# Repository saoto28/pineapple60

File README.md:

# pineapple60
ergonomic keyboard with Trackpoint

The purposes of this project.
- Install it in ThinkPad

## pineapple-F
Pinapple-Fold, Foldable ergonomic keyboard  
[mockup video on twitter](https://x.com/saoto28/status/2055436990498451473)

## pineapple-D
Pineapple-Deep, under consideration

## p60P
Pineapple60-Popup, installing a Pop-up keyboard on a ThinkPad.  

[Mockup video](https://youtu.be/z3uHgcyWICA)

## p60C
2026, Pineapple60-Convertible, Three-dimensional ergonomic arrangement and a flat, compact convertible. A patent allowed in Japan.

1st prototype 

[Video](https://x.com/saoto28/status/2051869687362077159)

Project repository: 
https://github.com/saoto28/pineapple60c.git

## p60S
2025, pineapple60s

Row-Staggered Ergonomic (Alice) keyboard with Kailh PG1316 for installing ThinkPad X13 Gen2

I forgot why it was named "S".

For this modification, I chose the target PC for the following reasons:
- It has a Trackpoint
- The keyboard can be easily replaced (the latest ThinkPads are getting difficult)
- The Trackpoint buttons should be on the case, not on the keyboard unit. Otherwise, I would need to attach the buttons to the keyboard I was making.

The following ThinkPads meet the above requirements:
- T440 to T460, and so on
- T460s and T470s
- X13 Gen2 and Gen3

X240 to X270 are also close, but we need to remove the motherboard to remove the keyboard.

Project repository: 
https://github.com/saoto28/pineapple60s.git

How to make (in Japanese): https://note.com/saoto28/n/n716b7ca2e1f9

## p0

Extra edition. Trackpoint module installation.

2021-10 Add the Trackpoint module of ThinkPad X100 on the Microsoft Ergonomic Keyboard.

[How to install the Trackpoint module in the MS ergonomic keyboard](p0/How_to_modify_MS_ergonomic_keyboard.pdf)

~~## p60X~~

~~Variable key layout board for researching ergonomic keyboard layouts~~

~~< 2021-09 coming soon >~~

## p50V

V-style key layout [board](p50V/README.md)

2021-08 installed on my T470s

## p60-03

third prototype [pcb](p60-03/README.md)

2021-05 p60-03b 

[how to make the ergonomic Trackpoint keyboard](how_to_make_ergonomic_trackpoint_keyboard.md)

## p4

2021-03 key layout testing [module](p4/README.md)

## p60-02

2020-12 second prototype [pcb](p60-02/README.md)

## p60-01

2020-10 first prototype [pcb](p60-01/README.md)

## pre-pineapple

2020-08 I tried to make an ergonomic keyboard for my ThinkPad T470s, by disassembling and modifying the spare keyboard. But, gave up.

## SNS

https://twitter.com/saoto28

https://www.reddit.com/user/saoto28/posts/

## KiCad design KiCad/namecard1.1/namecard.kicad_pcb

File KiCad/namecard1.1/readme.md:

# KiCAD format for the Arduino shield  namecard ver.1.1

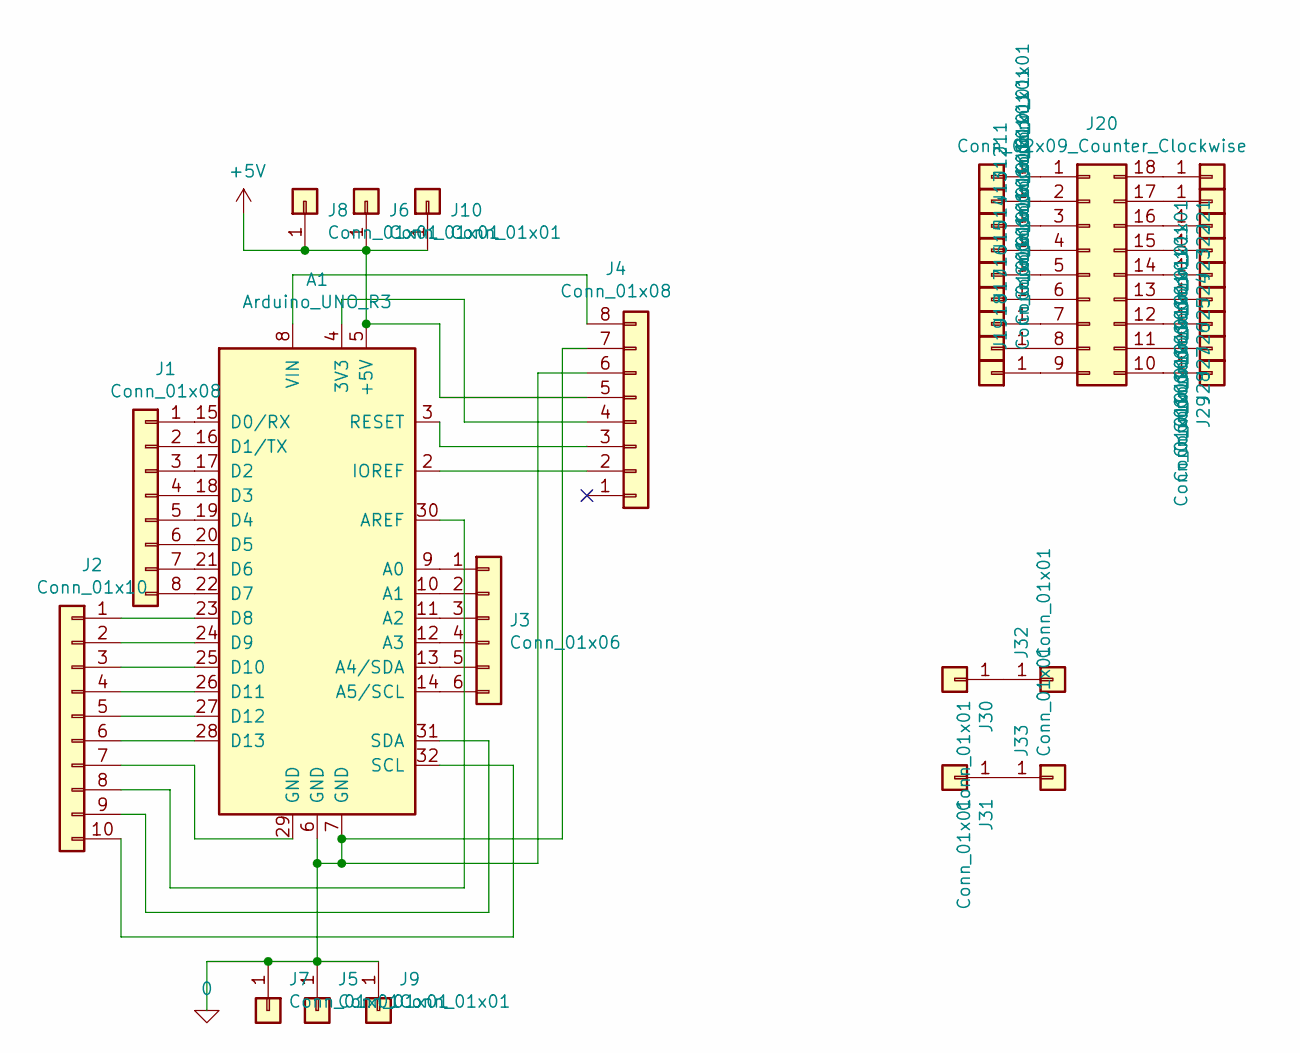
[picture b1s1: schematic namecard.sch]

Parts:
A1: Arduino_UNO_R3
J1, J4: Conn_01x08; PinHeader_1x08_P2.54mm_Vertical
J2: Conn_01x10; PinHeader_1x10_P2.54mm_Vertical
J3: Conn_01x06; PinHeader_1x06_P2.54mm_Vertical
J5, J6, J7, J8, J9, J10, J30, J31, J32, J33: Conn_01x01; SolderWirePad_1x01_Drill1.0mm_1.7
J11, J12, J13, J14, J15, J16, J17, J18, J19, J21, J22, J23, J24, J25, J26, J27, J28, J29: Conn_01x01; SolderWirePad_1x01_Drill1.0mm_1.7_no-mark
J20: Conn_02x09_Counter_Clockwise; SOP-18_7x12.5mm_P1.27mm_mod

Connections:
unnamed: A1.1 (NC), A1.29 (GND), J2.7
unnamed: A1.2 (IOREF), J4.2
unnamed: A1.3 (RESET), J4.3
unnamed: A1.4 (3V3), J4.4
unnamed: A1.8 (VIN), J4.8
unnamed: A1.9 (A0), J3.1
unnamed: A1.10 (A1), J3.2
unnamed: A1.11 (A2), J3.3
unnamed: A1.12 (A3), J3.4
unnamed: A1.13 (A4/SDA), J3.5
unnamed: A1.14 (A5/SCL), J3.6
unnamed: A1.15 (D0/RX), J1.1
unnamed: A1.16 (D1/TX), J1.2
unnamed: A1.17 (D2), J1.3
unnamed: A1.18 (D3), J1.4
unnamed: A1.19 (D4), J1.5
unnamed: A1.20 (D5), J1.6
unnamed: A1.21 (D6), J1.7
unnamed: A1.22 (D7), J1.8
unnamed: A1.23 (D8), J2.1
unnamed: A1.24 (D9), J2.2
unnamed: A1.25 (D10), J2.3
unnamed: A1.26 (D11), J2.4
unnamed: A1.27 (D12), J2.5
unnamed: A1.28 (D13), J2.6
unnamed: A1.30 (AREF), J2.8
unnamed: A1.31 (SDA), J2.9
unnamed: A1.32 (SCL), J2.10
unnamed: J11.1, J20.1
unnamed: J12.1, J20.2
unnamed: J13.1, J20.3
unnamed: J14.1, J20.4
unnamed: J15.1, J20.5
unnamed: J16.1, J20.6
unnamed: J17.1, J20.7
unnamed: J18.1, J20.8
unnamed: J19.1, J20.9
unnamed: J20.10, J29.1
unnamed: J20.11, J28.1
unnamed: J20.12, J27.1
unnamed: J20.13, J26.1
unnamed: J20.14, J25.1
unnamed: J20.15, J24.1
unnamed: J20.16, J23.1
unnamed: J20.17, J22.1
unnamed: J20.18, J21.1
unnamed: J30.1, J32.1
unnamed: J31.1, J33.1

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
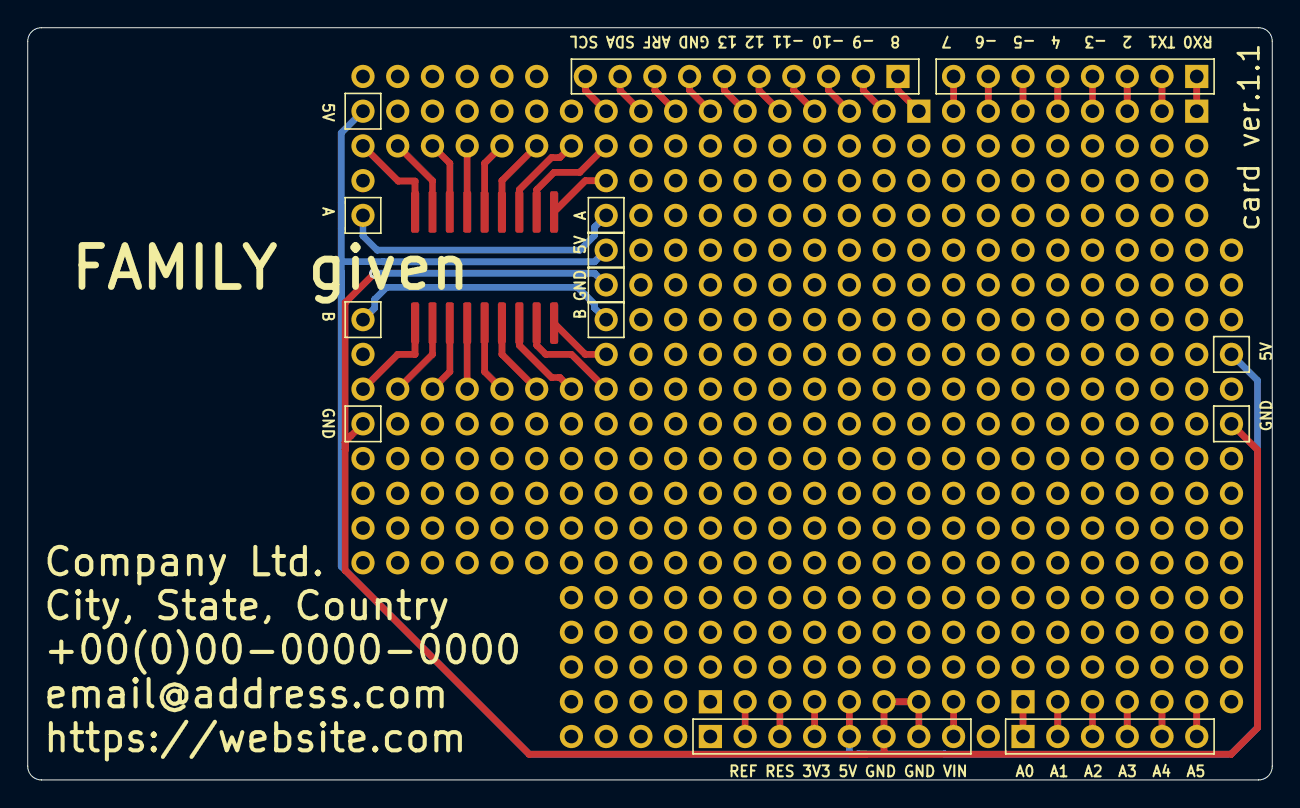
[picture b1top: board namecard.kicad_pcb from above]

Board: 2 copper layers, 91.0 x 55.0 mm, 34 parts (1 on the bottom side), 50 nets.

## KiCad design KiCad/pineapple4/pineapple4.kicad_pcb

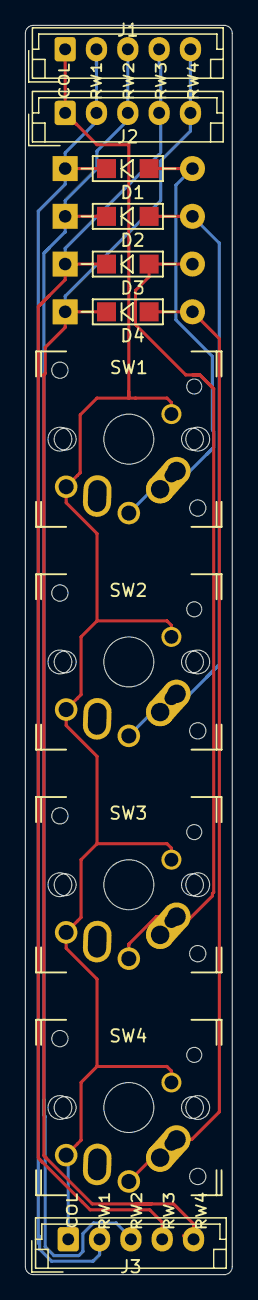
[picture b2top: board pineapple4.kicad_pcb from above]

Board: 2 copper layers, 16.5 x 99.7 mm, 11 parts (0 on the bottom side), 9 nets.

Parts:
D1, D2, D3, D4: D; Diode_TH_SOD123
J1, J2, J3: Conn_01x05; JST_EH_B5B-EH-A_1x05_P2.50mm_Vertical
SW1, SW2, SW3, SW4: SW_Push; MX-ALPS-Choc-X-straight-oneside

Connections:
unnamed: D1.1, J1.2, J2.2, J3.2
unnamed: D1.2, SW1.2
unnamed: D2.1, J1.3, J2.3, J3.3
unnamed: D2.2, SW2.2
unnamed: D3.1, J1.4, J2.4, J3.4
unnamed: D3.2, SW3.2
unnamed: D4.1, J1.5, J2.5, J3.5
unnamed: D4.2, SW4.2
unnamed: J1.1, J2.1, J3.1, SW1.1, SW2.1, SW3.1, SW4.1

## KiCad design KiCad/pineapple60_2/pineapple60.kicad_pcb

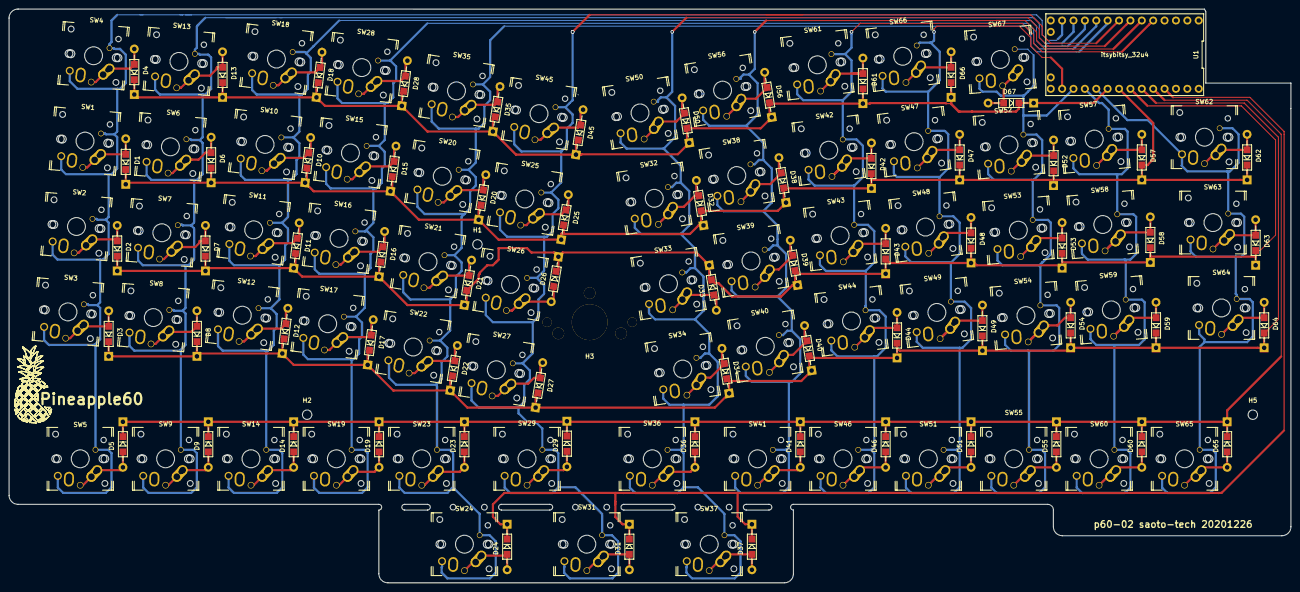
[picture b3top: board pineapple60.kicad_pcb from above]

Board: 2 copper layers, 286.0 x 128.0 mm, 137 parts (0 on the bottom side), 85 nets.

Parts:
D1, D2, D3, D4, D5, D6, D7, D8, D9, D10, D11, D12, D13, D14, D15, D16, D17, D18, D19, D20, D21, D22, D23, D24, D25, D26, D27, D28, D29, D31, D32, D33, D34, D35, D36, D37, D38, D39, D40, D41, D42, D43, D44, D45, D46, D47, D48, D49, D50, D51, D52, D53, D54, D55, D56, D57, D58, D59, D60, D61, D62, D63, D64, D65, D66, D67: D; Diode_TH_SOD123
H1, H2, H5: MountingHole; MountingHole_2.1mm
H3: MountingHole; Trackpoint_KT1255
SW1, SW2, SW3, SW4, SW5, SW6, SW7, SW8, SW9, SW10, SW11, SW12, SW13, SW14, SW15, SW16, SW17, SW18, SW19, SW20, SW21, SW22, SW23, SW25, SW26, SW27, SW28, SW31, SW32, SW33, SW34, SW35, SW38, SW39, SW40, SW41, SW42, SW43, SW44, SW45, SW46, SW47, SW48, SW49, SW50, SW51, SW52, SW53, SW54, SW55, SW56, SW57, SW58, SW59, SW60, SW61, SW65, SW66, SW67: SW_Push; MX-ALPS-Choc-X-straight-oneside
SW24, SW29, SW36, SW37, SW62, SW63, SW64: SW_Push; MX-ALPS-Choc-X-straight-1.5U
U1: itsybitsy_32u4; itsybitsy_32u4_open

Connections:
unnamed: D1.2, SW1.2
unnamed: D2.2, SW2.2
unnamed: D3.2, SW3.2
unnamed: D4.2, SW4.2
unnamed: D5.2, SW5.2
unnamed: D6.2, SW6.2
unnamed: D7.2, SW7.2
unnamed: D8.2, SW8.2
unnamed: D9.2, SW9.2
unnamed: D10.2, SW10.2
unnamed: D11.2, SW11.2
unnamed: D12.2, SW12.2
unnamed: D13.2, SW13.2
unnamed: D14.2, SW14.2
unnamed: D15.2, SW15.2
unnamed: D16.2, SW16.2
unnamed: D17.2, SW17.2
unnamed: D18.2, SW18.2
unnamed: D19.2, SW19.2
unnamed: D20.2, SW20.2
unnamed: D21.2, SW21.2
unnamed: D22.2, SW22.2
unnamed: D23.2, SW23.2
unnamed: D24.2, SW24.2
unnamed: D25.2, SW25.2
unnamed: D26.2, SW26.2
unnamed: D27.2, SW27.2
unnamed: D28.2, SW28.2
unnamed: D29.2, SW29.2
unnamed: D31.2, SW31.2
unnamed: D32.2, SW32.2
unnamed: D33.2, SW33.2
unnamed: D34.2, SW34.2
unnamed: D35.2, SW35.2
unnamed: D36.2, SW36.2
unnamed: D37.2, SW37.2
unnamed: D38.2, SW38.2
unnamed: D39.2, SW39.2
unnamed: D40.2, SW40.2
unnamed: D41.2, SW41.2
unnamed: D42.2, SW42.2
unnamed: D43.2, SW43.2
unnamed: D44.2, SW44.2
unnamed: D45.2, SW45.2
unnamed: D46.2, SW46.2
unnamed: D47.2, SW47.2
unnamed: D48.2, SW48.2
unnamed: D49.2, SW49.2
unnamed: D50.2, SW50.2
unnamed: D51.2, SW51.2
unnamed: D52.2, SW52.2
unnamed: D53.2, SW53.2
unnamed: D54.2, SW54.2
unnamed: D55.2, SW55.2
unnamed: D56.2, SW56.2
unnamed: D57.2, SW57.2
unnamed: D58.2, SW58.2
unnamed: D59.2, SW59.2
unnamed: D60.2, SW60.2
unnamed: D61.2, SW61.2
unnamed: D62.2, SW62.2
unnamed: D63.2, SW63.2
unnamed: D64.2, SW64.2
unnamed: D65.2, SW65.2
unnamed: D66.2, SW66.2
unnamed: D67.2, SW67.2
col0: SW1.1, SW2.1, SW3.1, SW4.1, SW5.1, U1.13
col1: SW6.1, SW7.1, SW8.1, SW9.1, SW13.1, U1.12
col2: SW10.1, SW11.1, SW12.1, SW14.1, SW18.1, U1.11
col3: SW15.1, SW16.1, SW17.1, SW19.1, SW28.1, U1.10
col4: SW20.1, SW21.1, SW22.1, SW23.1, SW24.1, SW35.1, U1.9
col5: SW25.1, SW26.1, SW27.1, SW29.1, SW31.1, SW45.1, U1.8
col6: SW32.1, SW33.1, SW34.1, SW36.1, SW37.1, SW50.1, U1.7
col7: SW38.1, SW39.1, SW40.1, SW41.1, SW56.1, U1.6
col8: SW42.1, SW43.1, SW44.1, SW46.1, SW61.1, U1.5
col9: SW47.1, SW48.1, SW49.1, SW51.1, SW66.1, U1.21
col10: SW52.1, SW53.1, SW54.1, SW55.1, SW67.1, U1.22
col11: SW57.1, SW58.1, SW59.1, SW60.1, U1.23
col12: SW62.1, SW63.1, SW64.1, SW65.1, U1.24
row0: D4.1, D13.1, D18.1, D28.1, D35.1, D45.1, D50.1, D56.1, D61.1, D66.1, D67.1, U1.25
row1: D1.1, D6.1, D10.1, D15.1, D20.1, D25.1, D32.1, D38.1, D42.1, D47.1, D52.1, D57.1, D62.1, U1.26
row2: D2.1, D7.1, D11.1, D16.1, D21.1, D26.1, D33.1, D39.1, D43.1, D48.1, D53.1, D58.1, D63.1, U1.27
row3: D3.1, D8.1, D12.1, D17.1, D22.1, D27.1, D34.1, D40.1, D44.1, D49.1, D54.1, D59.1, D64.1, U1.28
row4: D5.1, D9.1, D14.1, D19.1, D23.1, D29.1, D36.1, D41.1, D46.1, D51.1, D55.1, D60.1, D65.1, U1.29
row5: D24.1, D31.1, D37.1, U1.30

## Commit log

2020-11-03 create folders
2020-12-26 Add p60-01 data
2020-12-26 add p60-02 folder
2020-12-26 add p60-01/README.md
2021-01-02 mod
    mod
2021-01-08 Add qmk keyboard folder
2021-01-15 Add a pic of second proto
2021-01-15 Add the pic
2021-01-15 Edit how_to_make_ergonomic_thinkpad.md
2021-01-30 Add p60_2 Trackpoint keyboard pics
2021-02-01 Add the KiCad data of p60-2
2021-02-03 Add SNS links on README.md
2021-02-08 Edit how_to_make_ergonomic_trackpoint_keyboard.md
2021-02-09 modfy how to
2021-03-04 Add origin in README.md
2021-03-06 add a footprint for Kailh switch
2021-03-31 Add p4 (testing module)
2021-03-31 mod p4/README.md
2021-03-31 add pics of p4
2021-04-02 add examples for p4
2021-04-24 Add p60-03
2021-04-26 mod p60-02/README.md
2021-05-13 add p60-03 pics
2021-05-14 Edit how to make the keyboard
2021-05-15 edit the "how_to_make_ergonomic_trackpoint_keyboard.md"
2021-05-15 modify how-to
2021-06-05 add p60-03b
2021-06-08 add p60-03b data
2021-06-13 Update "How to make ergonomic Trackpoint keyboard"
2021-06-13 update qmk files
2021-06-13 update how to make
2021-06-13 add comments in keymaps
2021-06-13 mod keymap comments
2021-06-16 mod keymaps little bit Exvhange some pics
2021-06-20 Update how to
2021-06-26 add the pineapple-4 pcb cad data
2021-06-27 edit how to
2021-07-01 Change LICENSE
    GPL3 to MIT
2021-07-03 Change LICENSE, MIT to GPL2
    Because, qmk was under GPL2. (qmk in only software in this repository.)
2021-07-23 add p4/v-style
2021-07-23 Mod README.md
2021-08-19 add namecard KiCAD data
2021-08-19 add readme.md for KiCAD/namecard1.1/
2021-08-31 Add p50V
2021-09-11 add p50v information
2021-09-11 add p50v_sch.pdf
2021-09-20 update qmk/keymaps
2021-09-30 renewal how_to_make_ergonomic_trackpoint_keyboard.md
2021-10-01 mention about pre-pineapple in README.md
2021-10-01 rename a pic
2021-10-06 add p0
2021-12-05 add "how to install Trackpoint module in MS ergonomic keyboard"
2021-12-05 change htm to pdf
2021-12-27 add how to modify ms ergonomic keyboard htm files
2025-03-23 add new project "p60S" Row-Staggered Ergonomic keyboard for X13 Gen2
2025-03-23 revise typo
2025-04-20 update the pic of p60s
2025-04-20 add comments on p60s
2025-06-08 add p60s info on README.md
2025-07-27 add a pic of p60s
2025-07-27 Add p50P project on README.md
2025-07-27 Change p50P to p60P
2026-04-04 Add p60C
2026-04-13 add p60d
2026-05-08 add the prototype of p60c
2026-05-12 add p60p mockup
2026-05-17 add pineapple-Fold mockup info
